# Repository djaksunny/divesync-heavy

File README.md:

# DiveSync Heavy

An autonomous underwater depth-control vehicle built around an ESP32 and MS5837 depth sensor, using a linear actuator syringe mechanism (0–100mm stroke) for buoyancy-based depth control. This repo contains the firmware, hardware design files, and control software — including PID and reinforcement learning (TD3) controllers — developed as part of ongoing research under Umar.

## Hardware Overview

- **Depth sensing:** MS5837 pressure/depth sensor
- **Actuation:** Linear actuator-driven syringe mechanism, 0–100mm stroke, adjusts buoyancy by changing displaced volume
- **Compute:** ESP32, communicating over USB serial (115200 baud) with a host machine running the Python control stack
- **Control loop:** 20Hz telemetry/state/actuator loop, with an inner PID stabilizing actuator position and an outer controller (PID / BC / RL) setting the depth-tracking target

Full schematics, PCB layout, and BOM are under `/eda`.

## Repository Structure

```
divesync-heavy/
├── data/                     # Raw experiment logs, grouped by hardware/software version -- see "Experiment Data" below
├── eda/                      # KiCad schematic, PCB, BOM, and exported schematic PDF
├── firmware/                 # ESP32 firmware (PlatformIO project)
├── python/
│   ├── controllers/
│   │   ├── inner.py           # Inner PID loop — actuator position control
│   │   ├── manual.py          # Gamepad/keyboard manual control
│   │   ├── pid.py             # Outer PID depth controller
│   │   ├── rl.py              # TD3 (fully online) depth controller
│   │   └── waveform.py        # Square-wave setpoint/actuator generator
│   ├── core/
│   │   ├── experiment.py      # Experiment setup, handshake, state machine
│   │   ├── logger.py          # CSV logging (raw/processed/state)
│   │   ├── merger.py          # Merges state + processed CSVs into training_data.csv
│   │   ├── processor.py       # Depth filtering, actuator unit conversion
│   │   ├── serial_manager.py  # Serial I/O with the ESP32
│   │   ├── state.py           # Computes depth error, filtered velocity
│   │   └── telemetry.py       # Raw serial line parsing
│   ├── ml/
│   │   ├── reward.py              # TD3 reward function
│   │   ├── td3_env_spec.py        # Gym shape-declaration env for SB3 (also defines the fixed obs-normalization bounds)
│   │   ├── td3_model.zip          # Actively-training TD3 model (updated after each RL dive)
│   │   └── td3_replay_buffer.pkl  # Persisted replay buffer across dives
│   └── visualization/
│       ├── display.py         # Live Tkinter depth/setpoint/error display
│       └── plotter.py         # Post-dive matplotlib plotting (depth/actuator/motor voltage)
├── results/
│   ├── divesync-heavy-v1-results/   # Behavior cloning, cascaded PID, step response, sysid plots
│   ├── divesync-heavy-v2-results/   # Behavior cloning, cascaded PID (fixed/variable), RL (fixed/variable)
│   └── divesync-heavy-v3-results/   # Fully-online RL: early / failure / converged
├── main.py                    # Experiment entry point / main control loop
├── requirements.txt
├── .gitignore
└── README.md
```

## Control Strategies

Two outer-loop control strategies were implemented and compared:

1. **PID** — classical outer-loop depth PID feeding actuator position setpoints to the inner PID. Cascaded/nested PID across both loops was tested and found unstable (~99% of trials); the current architecture uses a single outer PID plus a fixed inner actuator-position PID instead.
2. **Reinforcement Learning (TD3)** — an off-policy, deterministic actor-critic algorithm (Twin Delayed DDPG), trained fully online on real hardware from a randomly-initialized actor and critics (no warm-start). Chosen over SAC/PPO/DDPG because its replay buffer suits the limited real-hardware sample budget, and its twin critics counter the Q-value overestimation that made vanilla DDPG unreliable.

### TD3 Implementation Notes

- Built on `stable_baselines3` (Gymnasium 1.3.0 / SB3 2.9.0), with a shape-only `DiveSyncEnvSpec` env used purely to satisfy SB3's constructor — no vectorized-env training loop is used. `main.py`'s own 20Hz loop *is* the environment loop; each dive is treated as one training episode.
- State inputs to the actor are normalized using the fixed bounds declared in `DiveSyncEnvSpec` (`OBS_LOW`/`OBS_HIGH`), not a data-fitted scaler.
- The reward function combines a depth-tracking error penalty, a velocity-damping penalty, and a smooth exponential barrier discouraging surfacing (and, in later iterations, an analogous barrier for the tank floor and an action-delta smoothness penalty).
- Both online (small periodic updates during a dive) and end-of-dive (`finalize()`, larger update) training were implemented; see **Known Issues** below regarding online training stability.
- Reward isn't logged during a dive. `python/reward_backfill.py` (gitignored, not part of the tracked pipeline) computes it after the fact from a run's `state.csv` (`depth_error_m`, `velocity_mps`) using the weights currently defined in `controllers/rl.py`, across every RL experiment under `data/` at once, writing a gitignored `reward.csv` / `reward_plot.png` per folder. Intent going forward is for `visualization/plotter.py` to compute this the same way but on the fly for a single experiment, rather than relying on a separate batch pass — not wired up yet.

## Running an Experiment

```bash
pip install -r requirements.txt
python main.py
```

You'll be prompted for:
- **Control mode:** `manual` / `pid` / `rl` / `sysid`
- **Experiment duration** (seconds)
- **Notes** (optional, stored in `metadata.json`)
- **COM port** for the ESP32

Each run creates a timestamped folder under `data/` containing `raw.csv`, `processed.csv`, `state.csv`, `boot.txt`, and `metadata.json`. After the experiment ends, `training_data.csv` is generated (merging `state.csv` and `processed.csv`), and a results plot is shown automatically if `processed.csv` exists.

The first `rl`-mode run initializes a fresh TD3 model (random actor + critics) since there is no warm-start; `python/ml/td3_model.zip` and `td3_replay_buffer.pkl` are created after `finalize()` and reused/extended on subsequent RL dives.

## Known Issues / Future Work

- **Online (mid-dive) training instability:** periodic training updates during a dive were found to occasionally collapse the policy into a degenerate constant-action output, likely due to the critic training on too little, too-correlated data early in a dive. Online training is currently disabled by default (`online_gradient_steps=0`); all TD3 updates happen in `finalize()`, once per dive. This was directly reproduced on the first fully-online (no warm-start) dive: the policy overshot to the tank floor, recovered, then froze at a near-constant near-minimum actuator output for the remaining ~9 minutes of a ~11-minute dive despite a large, persistent tracking error. `RLController` now has a `random_warmup_decisions` phase (default 50 decisions, ~50s) where actions are sampled randomly (still delta-clamped for hardware safety) instead of drawn from the untrained actor, so the critic sees diverse transitions before any training happens.
- **Reward scale sensitivity:** TD3 training was found to be highly sensitive to reward term magnitudes — a ~40x increase in one reward weight relative to another was sufficient to destabilize training into bang-bang actuator behavior. Current weights are tuned empirically; a more principled reward-normalization approach is a natural next step.
- **Residual steady-state tracking error:** the current TD3 policy shows a repeatable damped-oscillation response to setpoint changes, converging to a small but consistent depth offset rather than exact tracking. Believed limited primarily by the small amount of real-dive training data available; a larger and more diverse replay buffer (more dives, more setpoint variety) is the most likely path to improvement.

## Experiment Data

Raw experiment logs under `data/`, grouped to match the hardware/software progression documented in `/results`. Each leaf folder is one experiment run (`YYYYMMDD-HHMMSS`), containing `raw.csv`, `processed.csv`, `state.csv`, `boot.txt`, `metadata.json`, and (once merged) `training_data.csv`.

### `divesync-heavy-v1-data/` (2026-07-06 -- 2026-07-09, 14 dives)

Earliest hardware iteration (50mm actuator stroke). Manual piloting, initial PID characterization, step-response/system-ID runs, and the first behavior-cloning + BC-warmstarted-RL attempts. Corresponds to `results/divesync-heavy-v1-results/`.

### `divesync-heavy-v2-data/` (2026-07-10, 2026-07-14, 31 dives)

100mm actuator stroke. Manual piloting for BC training data, PID validation (fixed/variable setpoint), and BC-pretraining-warmstarted TD3 -- the warmstart approach later found to underperform and replaced in v3. Corresponds to `results/divesync-heavy-v2-results/`.

### `divesync-heavy-v3-data/` -- fully-online TD3, no BC warm-start

The BC/warmstart pipeline was removed; TD3 trains entirely online from real dives from here on. Corresponds to `results/divesync-heavy-v3-results/` (reinforcement-learning-early/failure/converged). Split into three subfolders:

- **`pid-validation/`** (2026-07-16, 11 dives) -- pure PID control-mode dives, re-validating the classical baseline on this hardware revision before RL work resumed.
- **`pre-swap/`** (2026-07-17, 23 dives) -- first fully-online TD3 dives on this hardware. Includes the full progression from cold-start collapse through the stuck-recovery and velocity-penalty fixes; best sustained result is `20260717-161502` (81% of samples within 0.05m of setpoint over a 10-minute dive).
- **`post-swap/`** (2026-07-21 -- 2026-07-22, 15 dives) -- after the actuator/buoyancy device was physically swapped, changing the depth dynamics enough to require a model reset (the pre-swap model/replay buffer no longer matched reality -- see `divesync-heavy-v3-data-incomplete-runs/README` for how that was diagnosed). Training restarted fully online on this dataset, converging faster than the original cold start since the warmup/stuck-recovery/reward fixes were already in place.

**Note for reuse:** `pre-swap` and `post-swap` reflect two physically different dynamical systems (same v3 software/methodology, different hardware buoyancy characteristics). Don't pool them for a single tracking-accuracy statistic without accounting for that split.

### `divesync-heavy-v3-data-incomplete-runs/`

Crashed/aborted experiments with no meaningful data (empty or header-only CSVs, no `metadata.json`) -- kept rather than deleted in case they're ever useful for debugging, but excluded from all of the above.

## Results

Comparison plots (behavior cloning, cascaded/fixed/variable PID, fixed/variable-setpoint RL, system identification, step response) are in `/results` and `/results/divesync-heavy-v1-results`.

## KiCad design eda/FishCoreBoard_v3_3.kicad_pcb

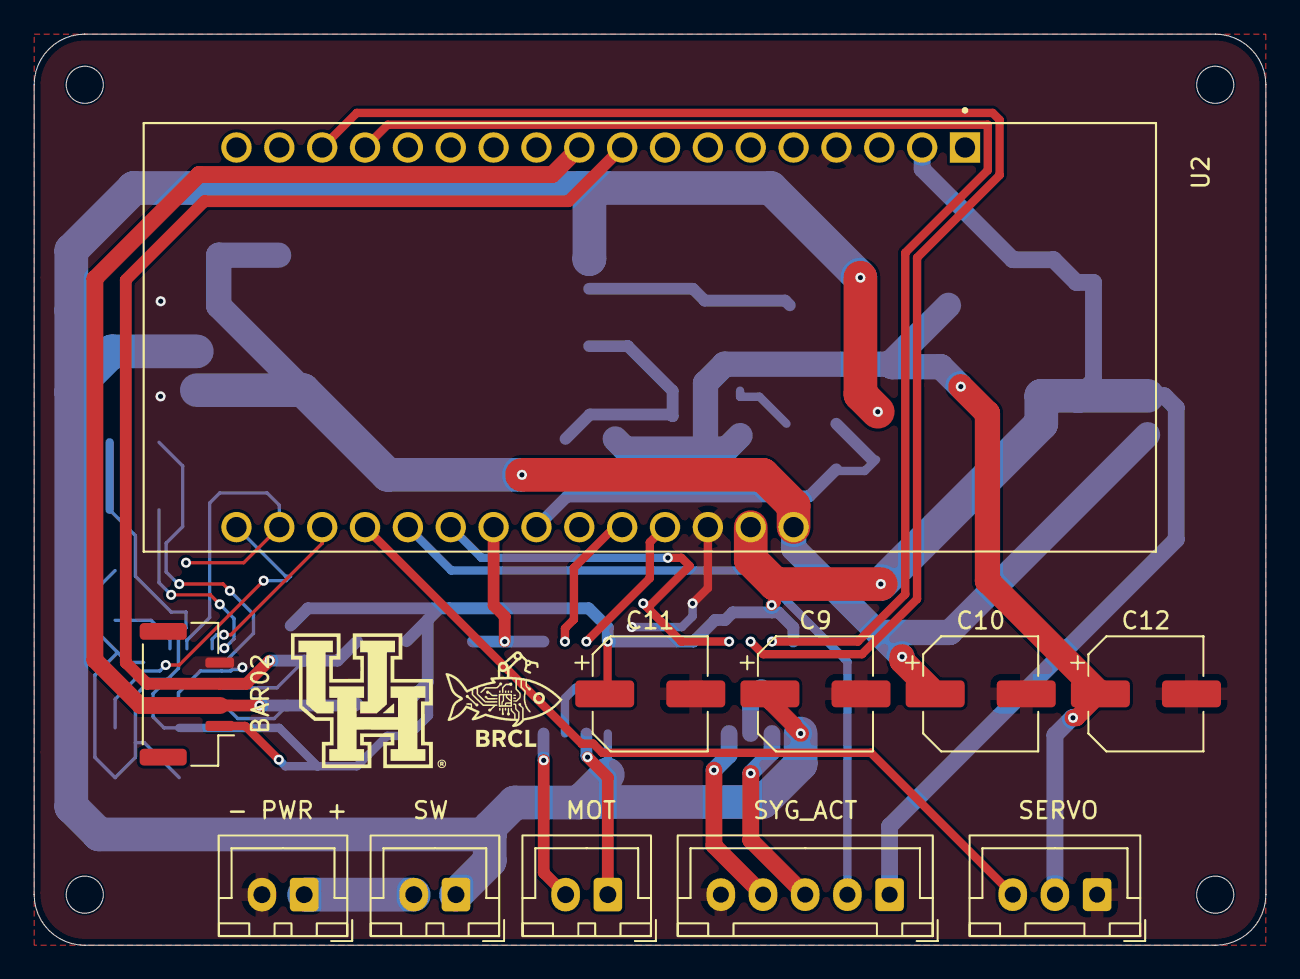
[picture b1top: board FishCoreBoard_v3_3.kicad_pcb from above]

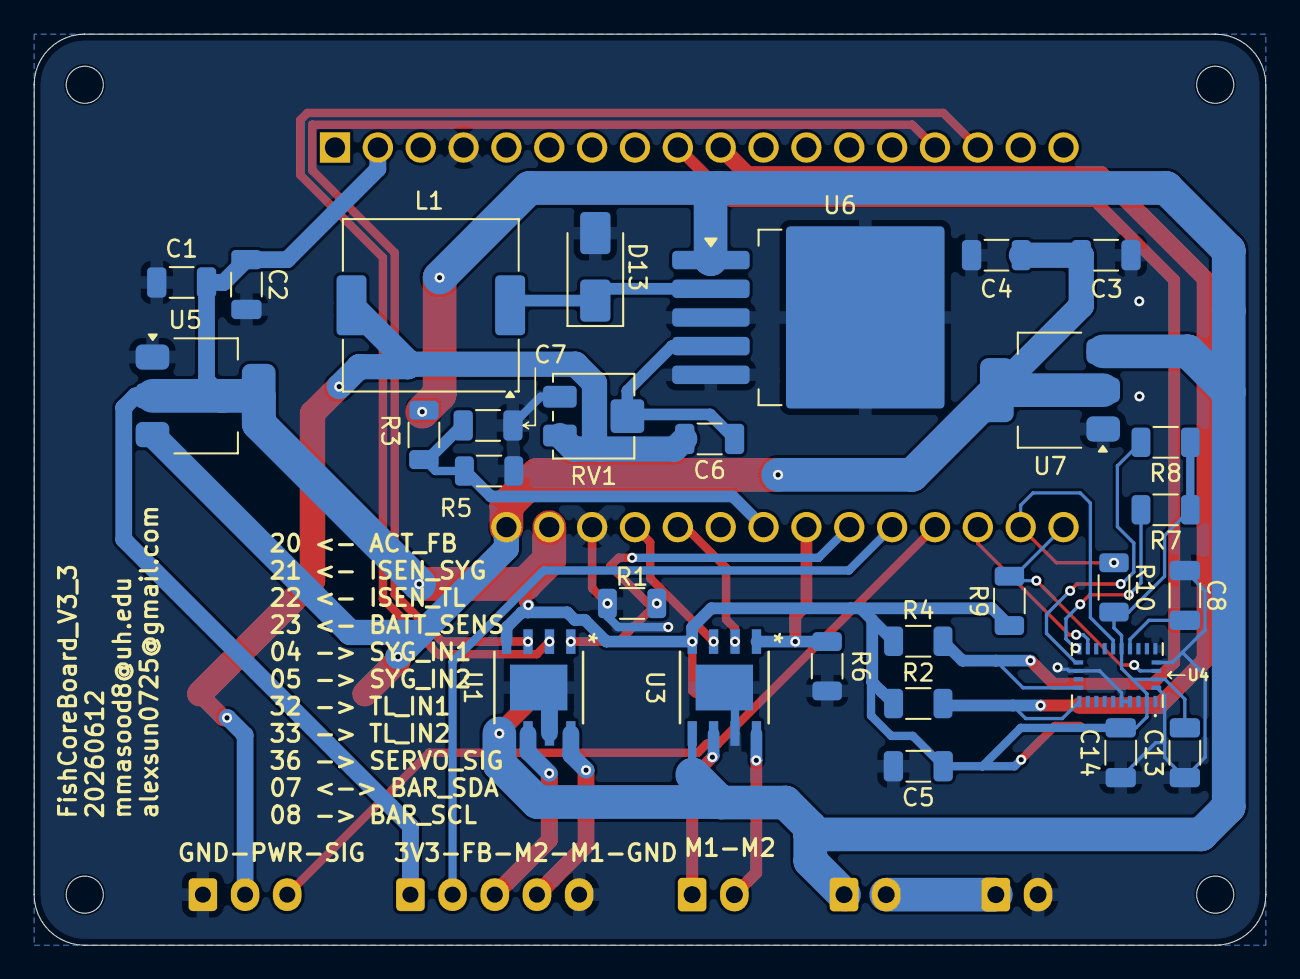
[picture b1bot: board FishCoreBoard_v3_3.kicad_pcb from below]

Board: 2 copper layers, 73.0 x 54.0 mm, 44 parts (29 on the bottom side), 29 nets.

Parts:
C1, C3, C8, C13, C14: 100nF; C_1206_3216Metric
C2, C4, C5, C7: 10uF; C_1206_3216Metric
C6: 220uF; C_1206_3216Metric
C9: 470uF; CP_Elec_6.3x4.5
C10, C11: 47uF; CP_Elec_6.3x4.5
C12: 220uF; CP_Elec_6.3x4.5
D13: B340AE-13; D_SMA
H1, H2, H3, H4: MountingHole; MountingHole_2.2mm_M2
J1, J3, J4: B2B_XH; JST_XH_B2B-XH-A_1x02_P2.50mm_Vertical
J2: Conn_01x05_Pin; JST_XH_B5B-XH-A_1x05_P2.50mm_Vertical
J5: Conn_01x03_Pin; JST_XH_B3B-XH-A_1x03_P2.50mm_Vertical
J6: BM04BGHS; JST_GH_BM04B-GHS-TBT_1x04-1MP_P1.25mm_Vertical
L1: 68uH; L_Coilcraft_MSS1048-XXX
R1, R2, R4, R6: 2K2; R_1206_3216Metric
R3: 4K7; R_1206_3216Metric
R5: 1K5; R_1206_3216Metric
R7, R8, R9, R10: 10kΩ; R_1206_3216Metric
RV1: R_Potentiometer; Potentiometer_Bourns_3214J_Horizontal
U1, U3: DRV8251ADDAR; SOIC8_DDA_TEX
U2: FireBeetle 2 ESP32-P4; MODULE_DFR0654
U4: BNO086; IC_BNO086
U5: AMS1117-3.3; SOT-223-3_TabPin2
U6: LM2596S-ADJ; TO-263-5_TabPin3
U7: AMS1117-5.0; SOT-223-3_TabPin2

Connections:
+3.3V: C1.1, C2.1, C5.1, C11.1, C13.2, C14.2, J2.1, J6.1, R2.1, R4.1, R7.1, R8.1, R9.1, R10.2, U1.4 (VREF), U2.2 (3.3V), U2.31 (3.3V), U3.4 (VREF), U4.3 (VDD), U4.10 (CLKSEL0), U4.28 (VDDIO), U5.2 (VO)
+5V: C3.1, C4.1, C10.1, U2.32 (VCC), U5.3 (VI), U7.2 (VO)
+12V: C9.1, J1.1, R3.1, U1.5 (VM), U3.5 (VM), U6.1 (VIN), U7.3 (VI)
/ACT_FB: J2.2, U2.23 (20)
/BATT_SENSE: C7.1, R3.2, R5.1, U2.26 (23)
/IMU_BOOT: R9.2, U2.19 (31), U4.4 (~BOOT)
/IMU_INT: U2.21 (35), U4.14 (~H_INT)
/IMU_RST: R10.1, U2.20 (34), U4.11 (~RST)
/ISEN_SYG: R1.2, U1.1 (IPROPI), U2.24 (21)
/ISEN_TL: R6.2, U2.25 (22), U3.1 (IPROPI)
/SCL: J6.3, R4.2, U2.9 (8/SCL), U4.19 (H_SCL/SCK/RX)
/SDA: J6.2, R2.2, U2.10 (7/SDA), U4.20 (H_SDA/H_MISO/TX)
/SERVO_PWR: C6.2, C12.1, J5.2, L1.2, RV1.1
/SERVO_SIG: J5.3, U2.22 (36)
/SYG_IN1: U1.3 (IN1), U2.15 (4)
/SYG_IN2: U1.2 (IN2), U2.16 (5)
/SYG_M1: J2.4, U1.8 (OUT2)
/SYG_M2: J2.3, U1.6 (OUT1)
/TL_IN1: U2.29 (32), U3.3 (IN1)
/TL_IN2: U2.28 (33), U3.2 (IN2)
/TL_M1: J4.1, U3.6 (OUT1)
/TL_M2: J4.2, U3.8 (OUT2)
GND: C1.2, C2.2, C3.2, C4.2, C5.2, C7.2, C8.1, C9.2, C10.2, C11.2, C12.2, C13.1, C14.1, D13.2 (A), J2.5, J3.2, J5.1, J6.4, R1.1, R5.2, R6.1, RV1.3, U1.7 (GND), U2.4 (GND), U2.30 (GND), U3.7 (GND), U4.2 (GND), U4.5 (PS1), U4.6 (PS0/WAKE), U4.17 (SA0/H_MOSI), U4.25 (GNDIO), U4.26 (XOUT32/CLKSEL1), U5.1 (GND), U6.3 (GND), U6.5 (~ON/OFF), U7.1 (GND)
unnamed: D13.1 (K), L1.1, U6.2 (OUT)
unnamed: J1.2, J3.1
unnamed: C8.2, U4.9 (CAP)
unnamed: R7.2, U4.15 (ENV_SCL)
unnamed: R8.2, U4.16 (ENV_SDA)
unnamed: C6.1, RV1.2, U6.4 (FB)

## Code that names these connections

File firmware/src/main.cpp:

#include <Arduino.h>
#include <Wire.h>
#include <MS5837.h>

// =========================
// Pin definitions
// =========================
#define SYG_IN1     4
#define SYG_IN2     5
#define SYG_FB      0       // Potentiometer feedback (analog in)
#define BAR_SDA     19
#define BAR_SCL     18
#define BATT_SENSE  3

// =========================
// Actuator limits
// =========================
#define SYG_MAX 4050        // Safe upper travel limit
#define SYG_MIN 400         // Safe lower travel limit

// =========================
// PWM settings (LEDC)
// =========================
#define PWM_FREQ    25000   // 25 kHz: above human hearing to eliminate whine
#define PWM_RES     8       // 8-bit resolution (0-255)
#define PWM_CH1     0       // LEDC hardware channel for IN1
#define PWM_CH2     1       // LEDC hardware channel for IN2

// =========================
// General settings
// =========================
#define NUM_SAMPLES_ACTUATOR        10
#define SERIAL_BAUD                 115200
#define TELEMETRY_PERIOD_MS         50
#define ATM_PRESSURE_MBAR           1024
#define DEPTH_SENSOR_REQUIRED       true

// =========================
// Battery ADC calibration
// =========================
#define ADC_MAX_COUNTS              4095.0f
#define ADC_REF_VOLTAGE             3.3f
#define BATT_DIVIDER_R_TOP_OHM      20000.0f
#define BATT_DIVIDER_R_BOTTOM_OHM   1500.0f

// =========================
// Fluid density
// =========================
const int FLUID_DENSITY = 1000;  // kg/m^3

// =========================
// Global state
// =========================
MS5837 BAR;

volatile int  g_motor_cmd      = 0;
unsigned long g_last_telemetry = 0;
bool          g_depth_ok       = false;

// =========================
// Function declarations
// =========================
int   getActuator(int n = NUM_SAMPLES_ACTUATOR);
void  actuate(int u);
void  processSerial();
void  sendTelemetry();
bool  updateDepthSensor(float &pressure_mbar, float &temperature_c, float &depth_m);
int   clampMotorCommand(int u);
float readBatteryVoltage();

// =========================
// Setup
// =========================
void setup() {
    pinMode(SYG_FB,     INPUT);
    pinMode(BATT_SENSE, INPUT);
    analogReadResolution(12);
    analogSetPinAttenuation(BATT_SENSE, ADC_0db);

    Serial.begin(SERIAL_BAUD);
    delay(200);

    // LEDC PWM init
    ledcSetup(PWM_CH1, PWM_FREQ, PWM_RES);
    ledcSetup(PWM_CH2, PWM_FREQ, PWM_RES);
    ledcAttachPin(SYG_IN1, PWM_CH1);
    ledcAttachPin(SYG_IN2, PWM_CH2);
    actuate(0);  // Brake on startup

    // Depth sensor init — blocks until ready if DEPTH_SENSOR_REQUIRED
    Wire.begin(BAR_SDA, BAR_SCL);

    do {
        if (BAR.init()) {
            BAR.setModel(MS5837::MS5837_02BA);
            BAR.setFluidDensity(FLUID_DENSITY);
            g_depth_ok = true;
            Serial.println("DEPTH_SENSOR_OK");
            break;
        }

        g_depth_ok = false;
        Serial.println("DEPTH_SENSOR_FAIL");

        if (DEPTH_SENSOR_REQUIRED) {
            Serial.println("WAITING_FOR_DEPTH_SENSOR");
            delay(500);
        }
    } while (DEPTH_SENSOR_REQUIRED);

    Serial.println("LOW_LEVEL_DEPTH_ACTUATOR_INTERFACE_READY");
}

// =========================
// Main loop
// =========================
void loop() {
    processSerial();
    actuate(g_motor_cmd);

    if (millis() - g_last_telemetry >= TELEMETRY_PERIOD_MS) {
        g_last_telemetry = millis();
        sendTelemetry();
    }
}

// =========================
// Serial command handling
// =========================
void processSerial() {
    if (!Serial.available()) return;

    String msg = Serial.readStringUntil('\n');
    msg.trim();
    if (msg.length() == 0) return;

    if (msg == "R") {
        sendTelemetry();
        return;
    }

    if (msg == "S") {
        g_motor_cmd = 0;
        actuate(0);
        Serial.println("ACK:STOP");
        return;
    }

    if (msg.startsWith("U:")) {
        int cmd = msg.substring(2).toInt();
        g_motor_cmd = clampMotorCommand(cmd);
        Serial.print("ACK:U:");
        Serial.println(g_motor_cmd);
        return;
    }

    if (msg == "RST") {
        ESP.restart();
    }

    Serial.print("ERR:UNKNOWN_CMD:");
    Serial.println(msg);
}

// =========================
// Telemetry output
// =========================
void sendTelemetry() {
    int   act_raw   = getActuator();
    float battery_v = readBatteryVoltage();

    float pressure_mbar = NAN;
    float temperature_c = NAN;
    float depth_m       = NAN;

    bool ok = updateDepthSensor(pressure_mbar, temperature_c, depth_m);

    // CSV: time_ms, actuator_raw, motor_cmd, depth_m, pressure_mbar, temp_c, depth_ok, battery_v
    Serial.print(millis());         Serial.print(",");
    Serial.print(act_raw);          Serial.print(",");
    Serial.print(g_motor_cmd);      Serial.print(",");
    Serial.print(depth_m, 4);       Serial.print(",");
    Serial.print(pressure_mbar, 2); Serial.print(",");
    Serial.print(temperature_c, 2); Serial.print(",");
    Serial.print(ok ? 1 : 0);       Serial.print(",");
    Serial.println(battery_v, 2);
}

// =========================
// Battery voltage read
// =========================
float readBatteryVoltage() {
    float v_sense     = analogReadMilliVolts(BATT_SENSE);
    float divider_gain = (BATT_DIVIDER_R_TOP_OHM + BATT_DIVIDER_R_BOTTOM_OHM)
                         / BATT_DIVIDER_R_BOTTOM_OHM;
    return v_sense * divider_gain / 1000.0f;
}

// =========================
// Depth sensor update
// =========================
bool updateDepthSensor(float &pressure_mbar, float &temperature_c, float &depth_m) {
    if (!g_depth_ok) return false;

    BAR.read();
    pressure_mbar = BAR.pressure();
    temperature_c = BAR.temperature();
    depth_m       = BAR.depth();

    return !(isnan(pressure_mbar) || isnan(temperature_c) || isnan(depth_m));
}

// =========================
// Actuator drive (DRV8251 via LEDC)
// =========================
void actuate(int u) {
    int pos = analogRead(SYG_FB);

    // Hard software travel limits
    if (pos >= SYG_MAX && u > 0) u = 0;
    if (pos <= SYG_MIN && u < 0) u = 0;

    u = constrain(u, -255, 255);

    if (u > 0) {                    // Extend
        ledcWrite(PWM_CH1, 0);
        ledcWrite(PWM_CH2, u);
    } else if (u < 0) {             // Retract
        ledcWrite(PWM_CH2, 0);
        ledcWrite(PWM_CH1, -u);
    } else {                        // Brake: both inputs HIGH
        ledcWrite(PWM_CH1, 255);
        ledcWrite(PWM_CH2, 255);
    }
}

// =========================
// Read actuator position (averaged)
// =========================
int getActuator(int n) {
    int sum = 0;
    for (int i = 0; i < n; i++) {
        sum += analogRead(SYG_FB);
    }
    return sum / n;
}

// =========================
// Clamp command to valid range
// =========================
int clampMotorCommand(int u) {
    return constrain(u, -255, 255);
}

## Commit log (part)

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2026-06-19 chore: organized PlatformIO and KiCad structure
2026-06-20 feat: added PWM functionality for actuator (-255 to 255)
2026-06-20 feat: added PID for actuator with GUI showing the PWM and PID
2026-06-22 chore: updated default parameters
2026-06-23 feat: added depth measuring and reading for interface and firmware
2026-06-25 feat: reworked firmware constants and added cascaded PID/waveform support to GUI
2026-06-25 chore: removed interface
2026-06-25 chore: updated firmware
2026-06-25 chore: fixed typo
2026-06-25 feat: added serial data logger with raw CSV export and updated firmware to reset upon serial connect
2026-06-25 fix: fully implemented JSON and added QoL and bug fixes
2026-06-25 chore: added README for DiveSync Heavy system documentation
2026-06-25 feat: updated logger and created manual gamepad control of PWM
2026-06-26 fix: fixed minor bugs regarding JSON formatting
2026-06-26 chore: updated gitignore and cleaned up data
2026-06-26 chore: organized structure and updated logger code
2026-06-26 chore: updated small QoL
2026-06-27 feat: improved structure and created core classes
2026-06-27 fix: updated experiment.py functions
2026-06-27 feat: finished all core classes
2026-06-28 fix: updated manual.py to match OOP structure
2026-06-28 chore: finalized file structure with experiment runner
2026-06-28 feat: finalized basic structure, manual control only
2026-06-29 fix: tweaked print logic and implemented battery voltage safeguard
2026-06-29 fix: updated main loop behavior to stop more accurately
2026-06-29 feat: added processor and updated logger accordingly
2026-06-29 chore: permanently untracked __pycache__ folders
2026-06-29 feat: implemented processor fully
2026-06-29 fix: updated rounding convention in processed actuator data
2026-06-30 feat: updated experiment to contain PID instead of MPC, created PID controller
2026-06-30 fix: updated classes to accommodate future additions (outer PID)
2026-06-30 feat: added waveform and polished files
